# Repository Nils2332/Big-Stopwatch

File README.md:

# Big-3D-Printed-Stopwatch

A simple 4 digit stopwatch triggered by 2 remote Buttons

Overview

Exploded Animation of the Main-Body
<br />
Demo of the running anmimation and rainbow highscore sign
## Built With
Counter powered by an ESP32 for future Extension with an Bluetooth App and more Functionalety.<br />
Programmeble WS2812 LEDs<br />
Remote Buttons: Custom PCB powered by an STM32F103<br />
Radio: nRF905 on 868 MHz band<br />

## License

This project is licensed under the MIT License

## Acknowledgments
* Inspiration @Jankae

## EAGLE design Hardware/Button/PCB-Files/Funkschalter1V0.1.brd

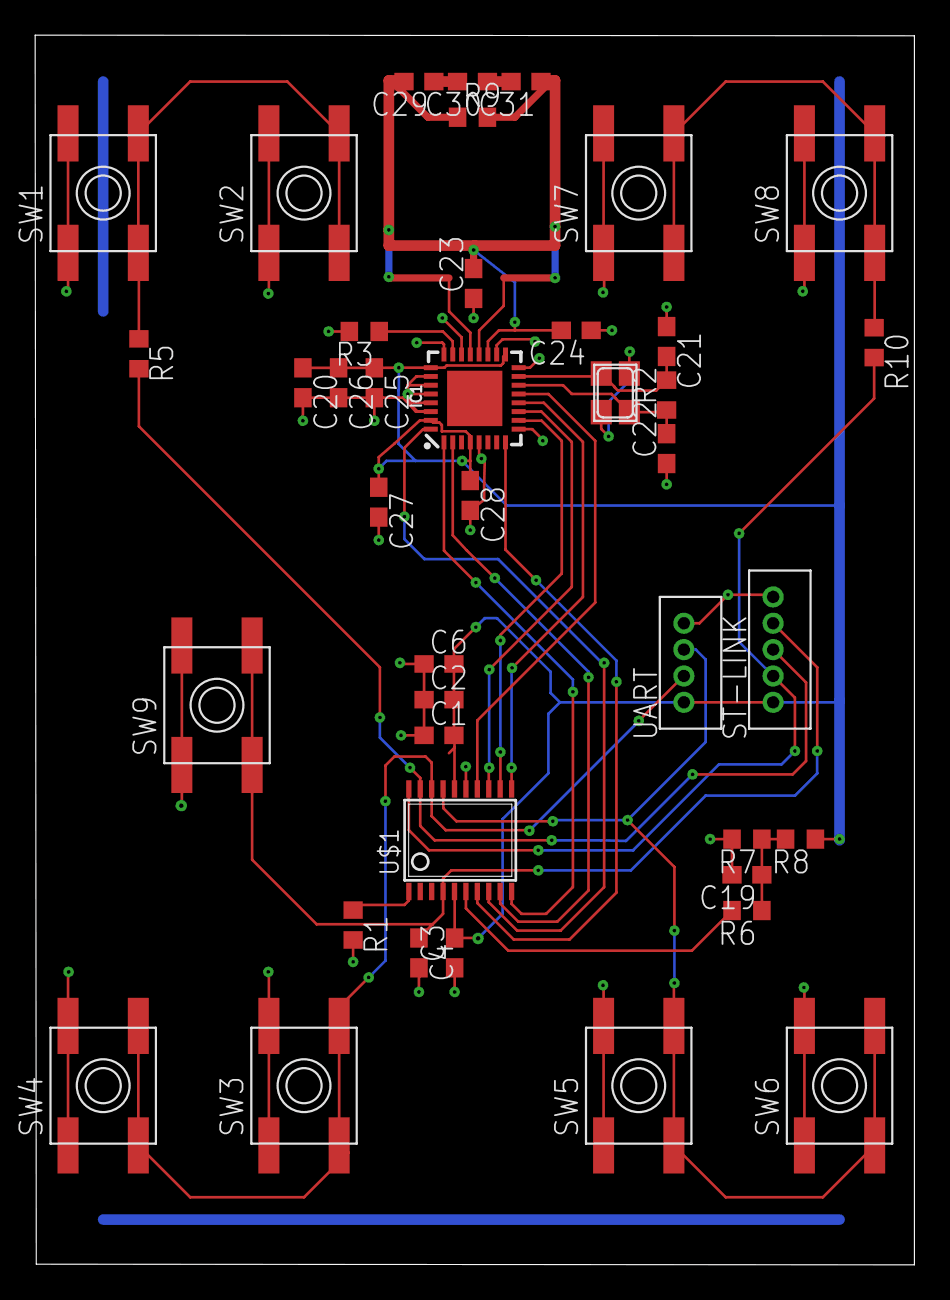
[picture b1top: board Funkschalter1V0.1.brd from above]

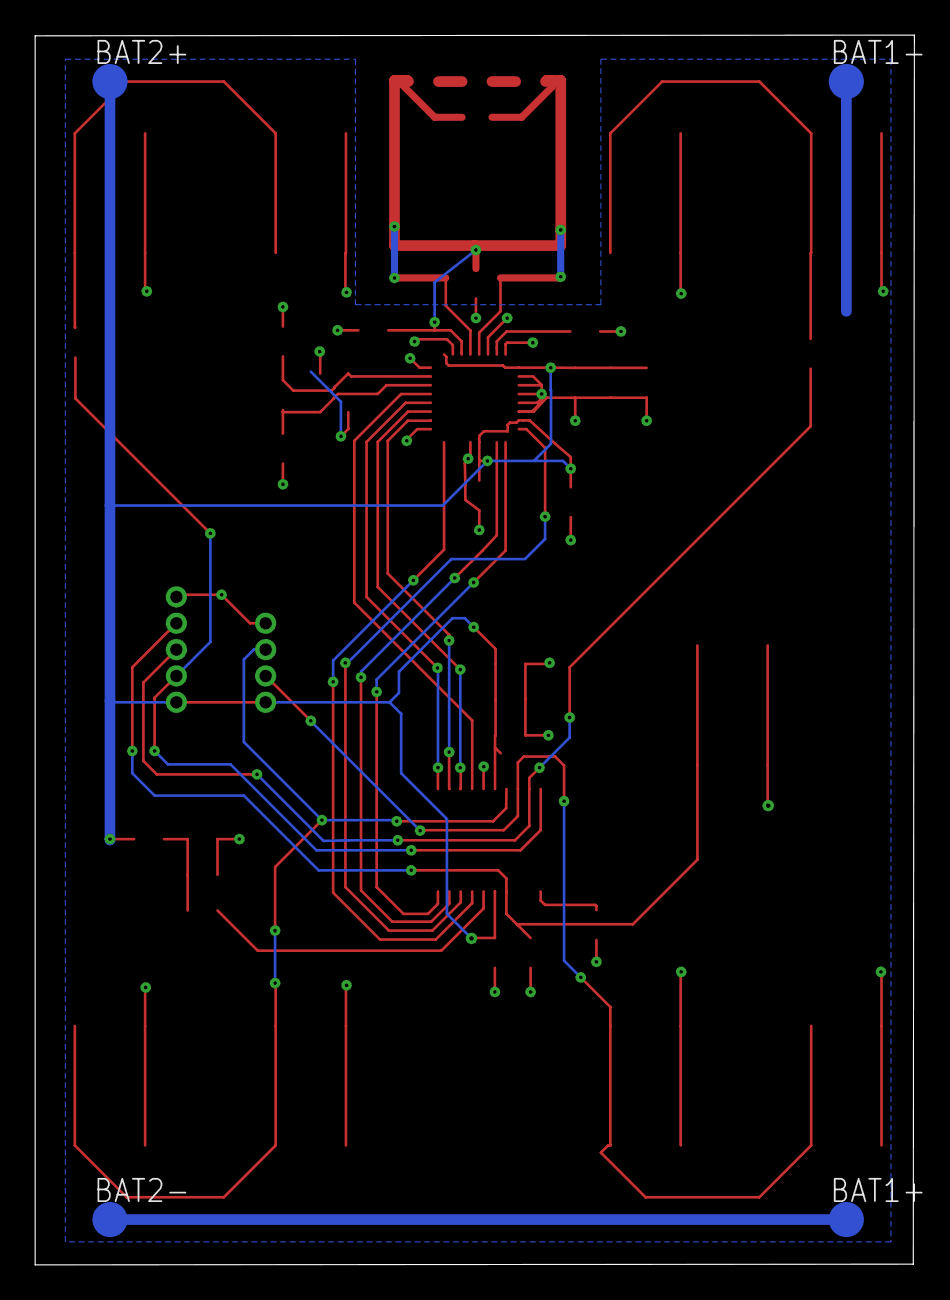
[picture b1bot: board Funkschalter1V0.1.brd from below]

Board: 2 copper layers, 50.0 x 70.0 mm, 45 parts (4 on the bottom side), 27 nets.

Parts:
BAT1+, BAT1-, BAT2+, BAT2-: TPTP20R; TP20R
C1, C2: 0.1uF; C0603
C3, C19, C27: 10nF; C0603
C4, C6: 4,7uF; C0603
C20: 4.7uF; C0603
C21, C22: 22pF; C0603
C23, C25, C26, C28: 33pF; C0603
C24: 3.3nF; C0603
C29: 5.6pF; C0603
C30: 4.7pF; C0603
C31: 3.9pF; C0603
IC1: nRF905; QFN32-5X5MM
Q1: X322516MRB4SI; NX3225
R1: 10k; R0603
R2: 1M; R0603
R3: 22k; R0603
R5, R10: 0; R0603
R6: 20k; R0603
R7: 100k; R0603
R8: 200k; R0603
R9: 18k; R0603
ST-LINK: B5B-ZR
SW1: K2-6639SP-C4SC-04; EVQ-Q2
SW2, SW3, SW4, SW5, SW6, SW7, SW8: TS; EVQ-Q2
SW9: SPST_TACT-EVQQ2; EVQ-Q2
U$1: STM32F030F4; TSSOP20
UART: B4B-ZR

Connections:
CSN: IC1.13, U$1.14
DR: IC1.8, U$1.7
GND: BAT1-.TP, C1.1, C2.1, C3.1, C4.2, C6.1, C19.2, C20.2, C21.1, C22.1, C23.1, C24.1, C25.2, C26.2, C27.2, C28.2, IC1.5, IC1.9, IC1.16, IC1.18, IC1.22, IC1.24, IC1.26, IC1.27, IC1.28, IC1.29, IC1.30, Q1.2, Q1.4, R1.2, R3.2, R7.2, ST-LINK.1, SW1.B, SW1.B', SW2.B, SW2.B', SW3.B, SW3.B', SW4.B, SW4.B', SW5.B, SW5.B', SW6.B, SW6.B', SW7.B, SW7.B', SW8.B, SW8.B', SW9.B, SW9.B', U$1.15, UART.1
MISO: IC1.10, U$1.12
MOSI: IC1.11, U$1.13
unnamed: R5.1, SW1.A, SW1.A', SW2.A, SW2.A'
unnamed: R1.1, U$1.1
unnamed: R6.2, U$1.6
unnamed: R10.1, SW7.A, SW7.A', SW8.A, SW8.A'
unnamed: BAT1+.TP, BAT2-.TP
unnamed: C19.1, R6.1, R7.1, R8.2
unnamed: C21.2, IC1.15, Q1.1, R2.2
unnamed: C22.2, IC1.14, Q1.3, R2.1
unnamed: IC1.23, R3.1
unnamed: C23.2, C24.2, C29.2, C31.1, IC1.19, IC1.20, IC1.21, R9.1, R9.2
unnamed: C30.1, C31.2
unnamed: C29.1, C30.2
NRST: C4.1, ST-LINK.2, SW9.A, SW9.A', U$1.4
PWRUP: IC1.2, U$1.9
SCK: IC1.12, U$1.11
SWCLK: R10.2, ST-LINK.4, U$1.20
SWDIO: R5.2, ST-LINK.3, U$1.19
TRX_CE: IC1.1, U$1.10
TX_EN: IC1.32, U$1.8
USART1_RX: SW3.A, SW3.A', SW4.A, SW4.A', U$1.18, UART.3
USART1_TX: SW5.A, SW5.A', SW6.A, SW6.A', U$1.17, UART.2
VCC: BAT2+.TP, C1.2, C2.2, C3.2, C6.2, C20.1, C25.1, C26.1, C27.1, C28.1, IC1.4, IC1.17, IC1.25, IC1.31, R8.1, ST-LINK.5, U$1.5, U$1.16, UART.4

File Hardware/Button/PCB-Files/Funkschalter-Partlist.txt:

Partlist

Exported from Funkschalter1V0.1.sch at 01.06.2018 23:58

EAGLE Version 9.0.0 Copyright (c) 1988-2018 Autodesk, Inc.

Assembly variant: 

Part     Value             Device            Package     Library     Sheet

BAT1+    TPTP20R           TPTP20R           TP20R       testpad     1
BAT1-    TPTP20R           TPTP20R           TP20R       testpad     1
BAT2+    TPTP20R           TPTP20R           TP20R       testpad     1
BAT2-    TPTP20R           TPTP20R           TP20R       testpad     1
C1       0.1uF             C-EUC0603         C0603       rcl         1
C2       0.1uF             C-EUC0603         C0603       rcl         1
C3       10nF              C-EUC0603         C0603       rcl         1
C4       4,7uF             C-EUC0603         C0603       rcl         1
C6       4,7uF             C-EUC0603         C0603       rcl         1
C19      10nF              C-EUC0603         C0603       rcl         1
C20      4.7uF             C-EUC0603         C0603       rcl         1
C21      22pF              C-EUC0603         C0603       rcl         1
C22      22pF              C-EUC0603         C0603       rcl         1
C23      33pF              C-EUC0603         C0603       rcl         1
C24      3.3nF             C-EUC0603         C0603       rcl         1
C25      33pF              C-EUC0603         C0603       rcl         1
C26      33pF              C-EUC0603         C0603       rcl         1
C27      10nF              C-EUC0603         C0603       rcl         1
C28      33pF              C-EUC0603         C0603       rcl         1
C29      5.6pF             C-EUC0603         C0603       rcl         1
C30      4.7pF             C-EUC0603         C0603       rcl         1
C31      3.9pF             C-EUC0603         C0603       rcl         1
IC1      nRF905            NRF905QFN32_5X5MM QFN32-5X5MM nordic-semi 1
Q1       X322516MRB4SI     XTAL-4-3225       NX3225      adafruit    1
R1       10k               R-EU_R0603        R0603       rcl         1
R2       1M                R-EU_R0603        R0603       rcl         1
R3       22k               R-EU_R0603        R0603       rcl         1
R4       10k               R-EU_R0603        R0603       rcl         1
R5       0                 R-EU_R0603        R0603       rcl         1
R6       20k               R-EU_R0603        R0603       rcl         1
R7       100k              R-EU_R0603        R0603       rcl         1
R8       200k              R-EU_R0603        R0603       rcl         1
R9       18k               R-EU_R0603        R0603       rcl         1
R10      0                 R-EU_R0603        R0603       rcl         1
ST-LINK  B5B-ZR            B5B-ZR            B5B-ZR      jst         1
SW1      K2-6639SP-C4SC-04 SPST_TACT-EVQQ2   EVQ-Q2      adafruit    1
SW2      TS                SPST_TACT-EVQQ2   EVQ-Q2      adafruit    1
SW3      TS                SPST_TACT-EVQQ2   EVQ-Q2      adafruit    1
SW4      TS                SPST_TACT-EVQQ2   EVQ-Q2      adafruit    1
SW5      TS                SPST_TACT-EVQQ2   EVQ-Q2      adafruit    1
SW6      TS                SPST_TACT-EVQQ2   EVQ-Q2      adafruit    1
SW7      TS                SPST_TACT-EVQQ2   EVQ-Q2      adafruit    1
SW8      TS                SPST_TACT-EVQQ2   EVQ-Q2      adafruit    1
SW9      SPST_TACT-EVQQ2   SPST_TACT-EVQQ2   EVQ-Q2      adafruit    1
U$1      STM32F030F4       STM32F030F4       TSSOP20     stm32f030f4 1
UART     B4B-ZR            B4B-ZR            B4B-ZR      jst         1

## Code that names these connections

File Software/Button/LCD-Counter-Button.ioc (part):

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Mcu.Name=STM32F030F4Px
Mcu.Package=TSSOP20
Mcu.UserName=STM32F030F4Px
PA0.Signal=GPIO_Output
PA1.GPIOParameters=GPIO_PuPd,GPIO_Label
PA1.GPIO_Label=DR
PA1.GPIO_PuPd=GPIO_PULLDOWN
PA1.Signal=GPIO_Input
PA10.Mode=Asynchronous
PA10.Signal=USART1_RX
PA13.GPIOParameters=GPIO_PuPd,GPIO_Label,GPIO_ModeDefaultEXTI
PA13.GPIO_Label=Button1
PA13.GPIO_ModeDefaultEXTI=GPIO_MODE_IT_FALLING
PA13.GPIO_PuPd=GPIO_PULLUP
PA13.Signal=GPXTI13
PA14.GPIOParameters=GPIO_PuPd,GPIO_Label,GPIO_ModeDefaultEXTI
PA14.GPIO_Label=Button2
PA14.GPIO_ModeDefaultEXTI=GPIO_MODE_IT_FALLING
PA14.GPIO_PuPd=GPIO_PULLUP
PA14.Signal=GPXTI14
PA2.GPIOParameters=GPIO_PuPd,GPIO_Label
PA2.GPIO_Label=TX_EN
PA2.GPIO_PuPd=GPIO_PULLUP
PA2.Signal=GPIO_Output
PA3.GPIOParameters=GPIO_PuPd,GPIO_Label
PA3.GPIO_Label=PWRUP
PA3.GPIO_PuPd=GPIO_PULLUP
PA3.Signal=GPIO_Output
PA4.GPIOParameters=GPIO_PuPd,GPIO_Label
PA4.GPIO_Label=TRX_CE
PA4.GPIO_PuPd=GPIO_PULLUP
PA4.Signal=GPIO_Output
PA5.GPIOParameters=GPIO_PuPd
PA5.GPIO_PuPd=GPIO_NOPULL
PA5.Mode=Full_Duplex_Master
PA5.Signal=SPI1_SCK
PA6.GPIOParameters=GPIO_PuPd
PA6.GPIO_PuPd=GPIO_NOPULL
PA6.Mode=Full_Duplex_Master
PA6.Signal=SPI1_MISO
PA7.GPIOParameters=GPIO_PuPd
PA7.GPIO_PuPd=GPIO_NOPULL
PA7.Mode=Full_Duplex_Master
PA7.Signal=SPI1_MOSI
PA9.Mode=Asynchronous
PA9.Signal=USART1_TX
PB1.GPIOParameters=PinState,GPIO_PuPd,GPIO_Label
PB1.GPIO_Label=CSN
PB1.GPIO_PuPd=GPIO_PULLUP
PB1.PinState=GPIO_PIN_SET
PB1.Signal=GPIO_Output
PF0-OSC_IN.Signal=GPIO_Output
PF1-OSC_OUT.Signal=GPIO_Output
RCC.SYSCLKFreq_VALUE=48000000
RCC.SYSCLKSource=RCC_SYSCLKSOURCE_PLLCLK
board=custom

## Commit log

2018-10-01 sorting
2018-10-01 GITIGNORE und GITATTRIBUTES hinzufügen.
2018-10-01 Projektdateien hinzufügen.
2018-10-01 test1
2018-10-02 Fixing tolerances
2018-10-02 junk deleted
2018-10-03 Bugfix
2018-10-03 working LEDLCD
2018-10-03 Debug
2018-10-03 show bat
2018-10-03 add colors
2018-10-04 adc update
2018-10-04 Working step 1
2018-10-05 Simple Stopwatch Working
2018-10-05 stoptime fix
2019-07-26 pictures
2019-07-26 edit
2019-07-26 Gif test
2019-07-28 Add PCB Button,
    Button Code,
    Rearrange
2019-07-28 Inital dummy commit
2019-07-28 Clean up initial file
2019-07-28 Move old_a files into subdir
2019-07-28 Move old_b files into subdir
2019-07-28 re-arrange
2019-07-28 gif rezise
2019-07-28 edit README
